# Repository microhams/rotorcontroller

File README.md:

rotorcontroller
===============

Antenna rotor controller for amateur radio. Based on Beagle Bone Black

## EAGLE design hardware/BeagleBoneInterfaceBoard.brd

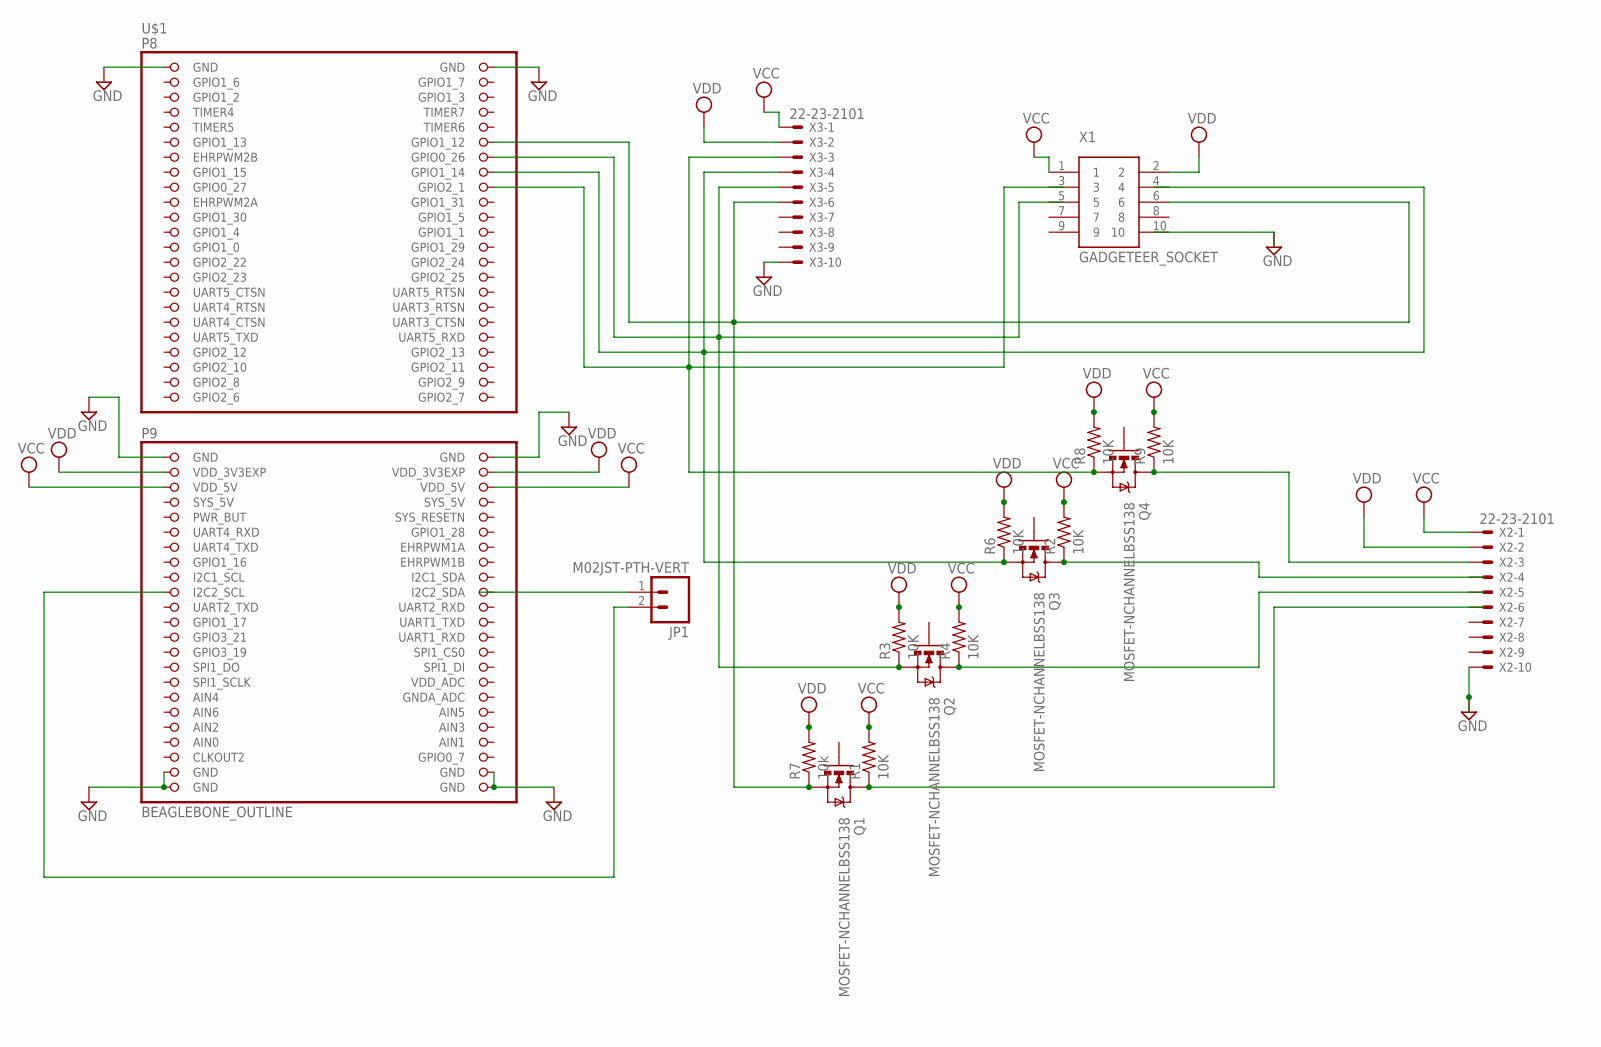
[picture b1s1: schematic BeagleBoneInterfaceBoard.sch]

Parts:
JP1: M02JST-PTH-VERT; JST-2-PTH-VERT
Q1, Q2, Q3, Q4: MOSFET-NCHANNELBSS138; SOT23
R1, R2, R3, R4, R6, R8, R9: 10K; R1210
R7: 10k; R1210
U$1: BEAGLEBONE_OUTLINE; BEAGLEBONE_SHIELD
X1: GADGETEER_SOCKET; SAMTEC_ESHF_2X5_1.27MM_LONG
X2, X3: 22-23-2101

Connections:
AIN0: U$1.85 (AIN0)
GND: U$1.1 (GND), U$1.2 (GND), U$1.47 (GND), U$1.48 (GND), U$1.89 (GND), U$1.90 (GND), U$1.91 (GND), U$1.92 (GND), X2.10
unnamed: Q3.2 (S), R6.1, U$1.16 (GPIO1_14), X3.4
unnamed: Q4.2 (S), R8.1, U$1.18 (GPIO2_1), X3.3
unnamed: Q1.2 (S), R7.1, U$1.12 (GPIO1_12), X1.6, X3.6
unnamed: Q2.2 (S), R3.1, U$1.14 (GPIO0_26), X3.5
unnamed: JP1.2, U$1.65 (I2C2_SCL)
unnamed: Q3.3 (D), R2.1
unnamed: Q1.3 (D), R1.1
unnamed: Q2.3 (D), R4.1
unnamed: Q4.3 (D), R9.1, X2.3
SYS_5V: U$1.53 (SYS_5V)
VCC: R1.2, R4.2, R9.2, U$1.51 (VDD_5V), U$1.52 (VDD_5V), X1.1, X2.1, X3.1
VDD: R3.2, R7.2, R8.2, U$1.49 (VDD_3V3EXP), U$1.50 (VDD_3V3EXP), X1.2, X2.2, X3.2

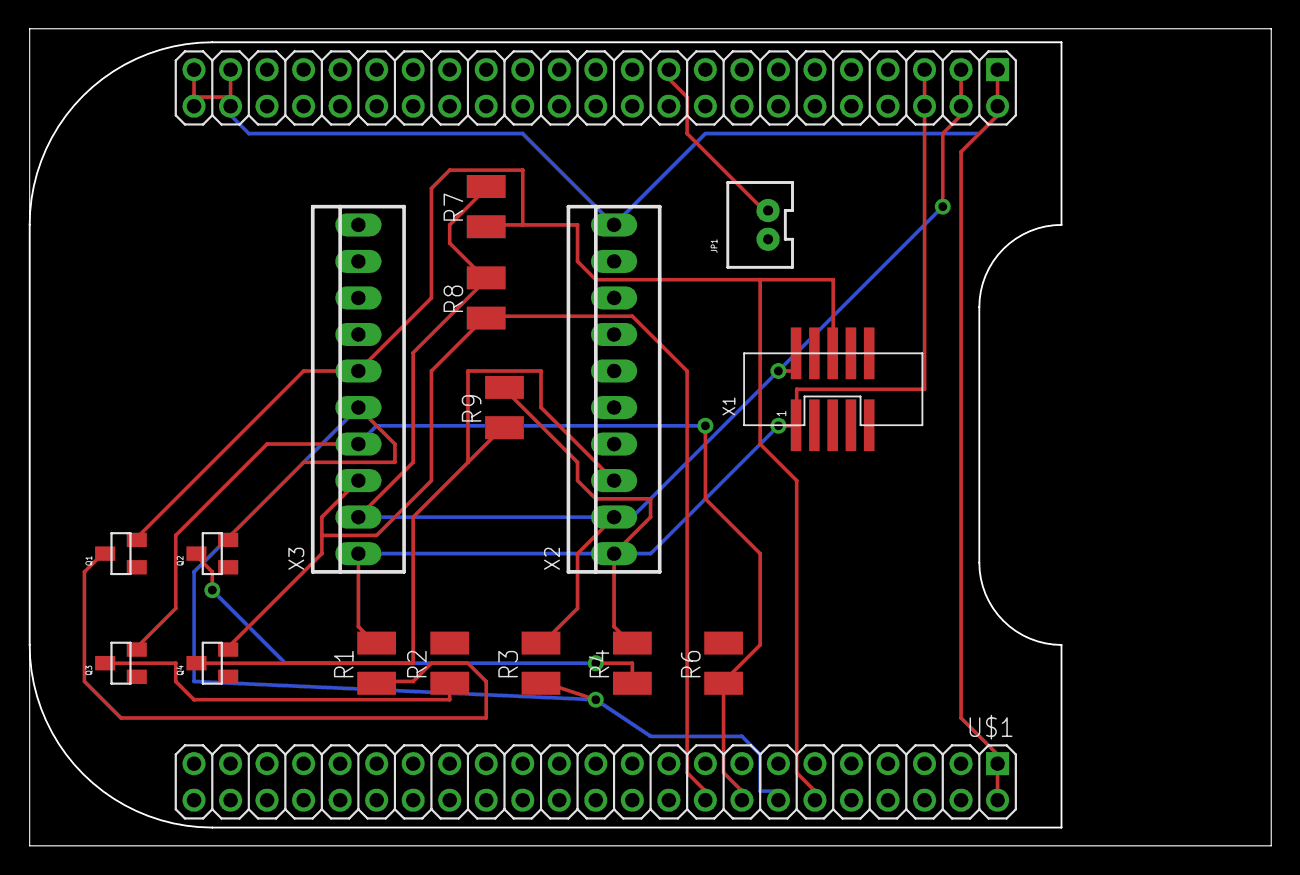
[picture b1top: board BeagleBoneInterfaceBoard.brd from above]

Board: 2 copper layers, 86.3 x 56.7 mm, 17 parts (0 on the bottom side), 12 nets.

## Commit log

2014-03-09 fix BBB name typo
2014-12-16 Rotor_Control_V1.0
    Rotor Controller Board V1
2014-12-17 move interface design files
2015-01-16 Updates to board after gerber review. Moved one via to provide more clearence
2015-01-20 Added Drill Layer and BOM updates
2015-01-20 Rotor Cost Analysis
2015-04-05 BBB schematics as pdf

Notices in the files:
parts and their libraries:
SparkFun-DiscreteSemi: Licensing: CC v3.0 Share-Alike You are welcome to use this library for commercial purposes.
